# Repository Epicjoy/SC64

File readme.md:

# SummerCart64 - a fully open source N64 flashcart

This project's hardware and casing are modified based on the [SummerCart64](https://github.com/Polprzewodnikowy/SummerCart64) project.

### Description

Experience classic gaming in a new way! SummerCart64 is a fully open-source flash cartridge designed for the Nintendo 64 (N64), perfect for both gamers and developers. Whether you want to relive your childhood memories or develop your own homebrew games, SummerCart64 has you covered.

### Features

-   **Extremely high game compatibility:** Supports N64 games up to 64MB (512Mb), covering the entire N64 game library
-  **Fast I/O**: Supports fast data transfer to ensure smooth gaming experiences，Thanks to a peak transfer rate of approximately 23.8 MiB/s, loading a maximum size game of **64MB** (512Mb) takes roughly 2.7 seconds under optimal conditions
- **RTC Functionality**: Built-in Real-Time Clock (**RTC**) to support games that require time functions.
-  **High-Capacity SD Card Support**: Supports microSD cards up to 2TB, allowing you to store more games and files.
-  **64DD Hardware Emulation**: It can play disk dumps directly! Combo games (N64 cartridge + 64DD disk) and multi-disk 64DD games are also supported.
- **Automatic Save Backup**: Automatically backs up saves during gameplay to protect your progress.
-  **Multi-Region Support**: Compatible with all region N64 consoles, eliminating region lock concerns.
-  **Enough space for your ROMs**: Equipped with **64 MiB SDRAM** and **16 MiB flash** memory to ensure smooth game operation.
-  **Easy Game Management**: Browse, run, and manage your game library directly on your N64 console with the intuitive N64FlashcartMenu.
-  **Full control of boot process:** perfect for trying out custom **IPL3** replacements giving you control right after N64 boots up

### Example

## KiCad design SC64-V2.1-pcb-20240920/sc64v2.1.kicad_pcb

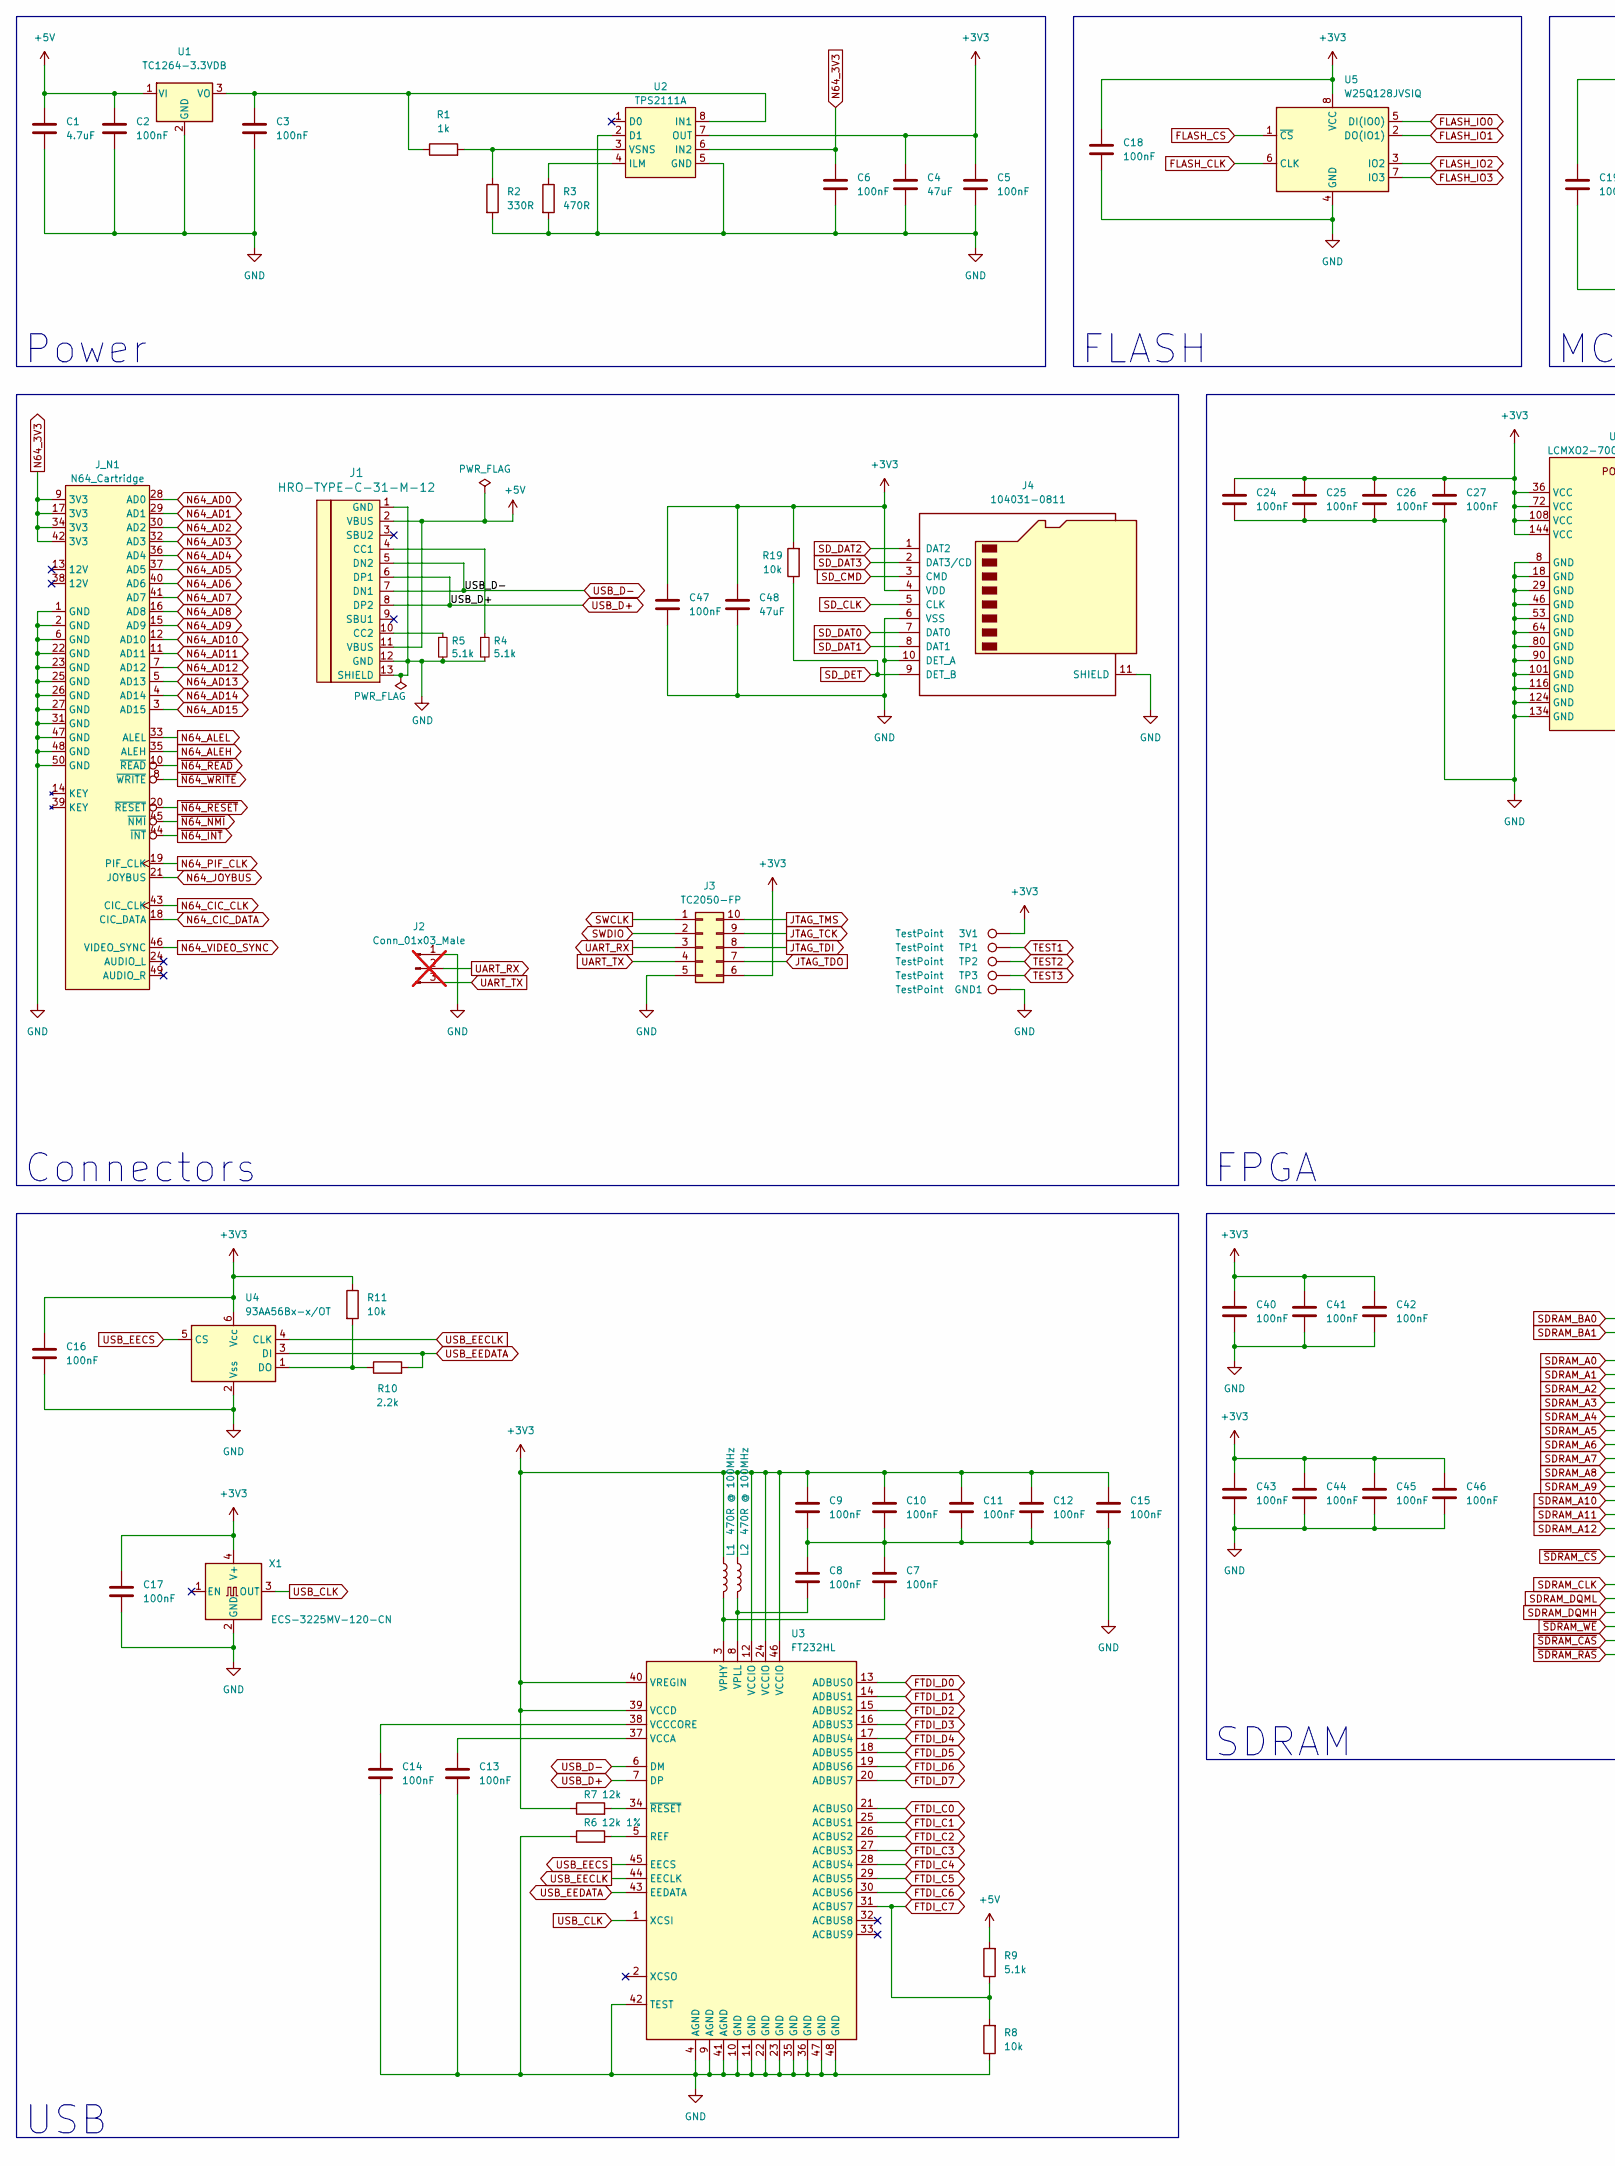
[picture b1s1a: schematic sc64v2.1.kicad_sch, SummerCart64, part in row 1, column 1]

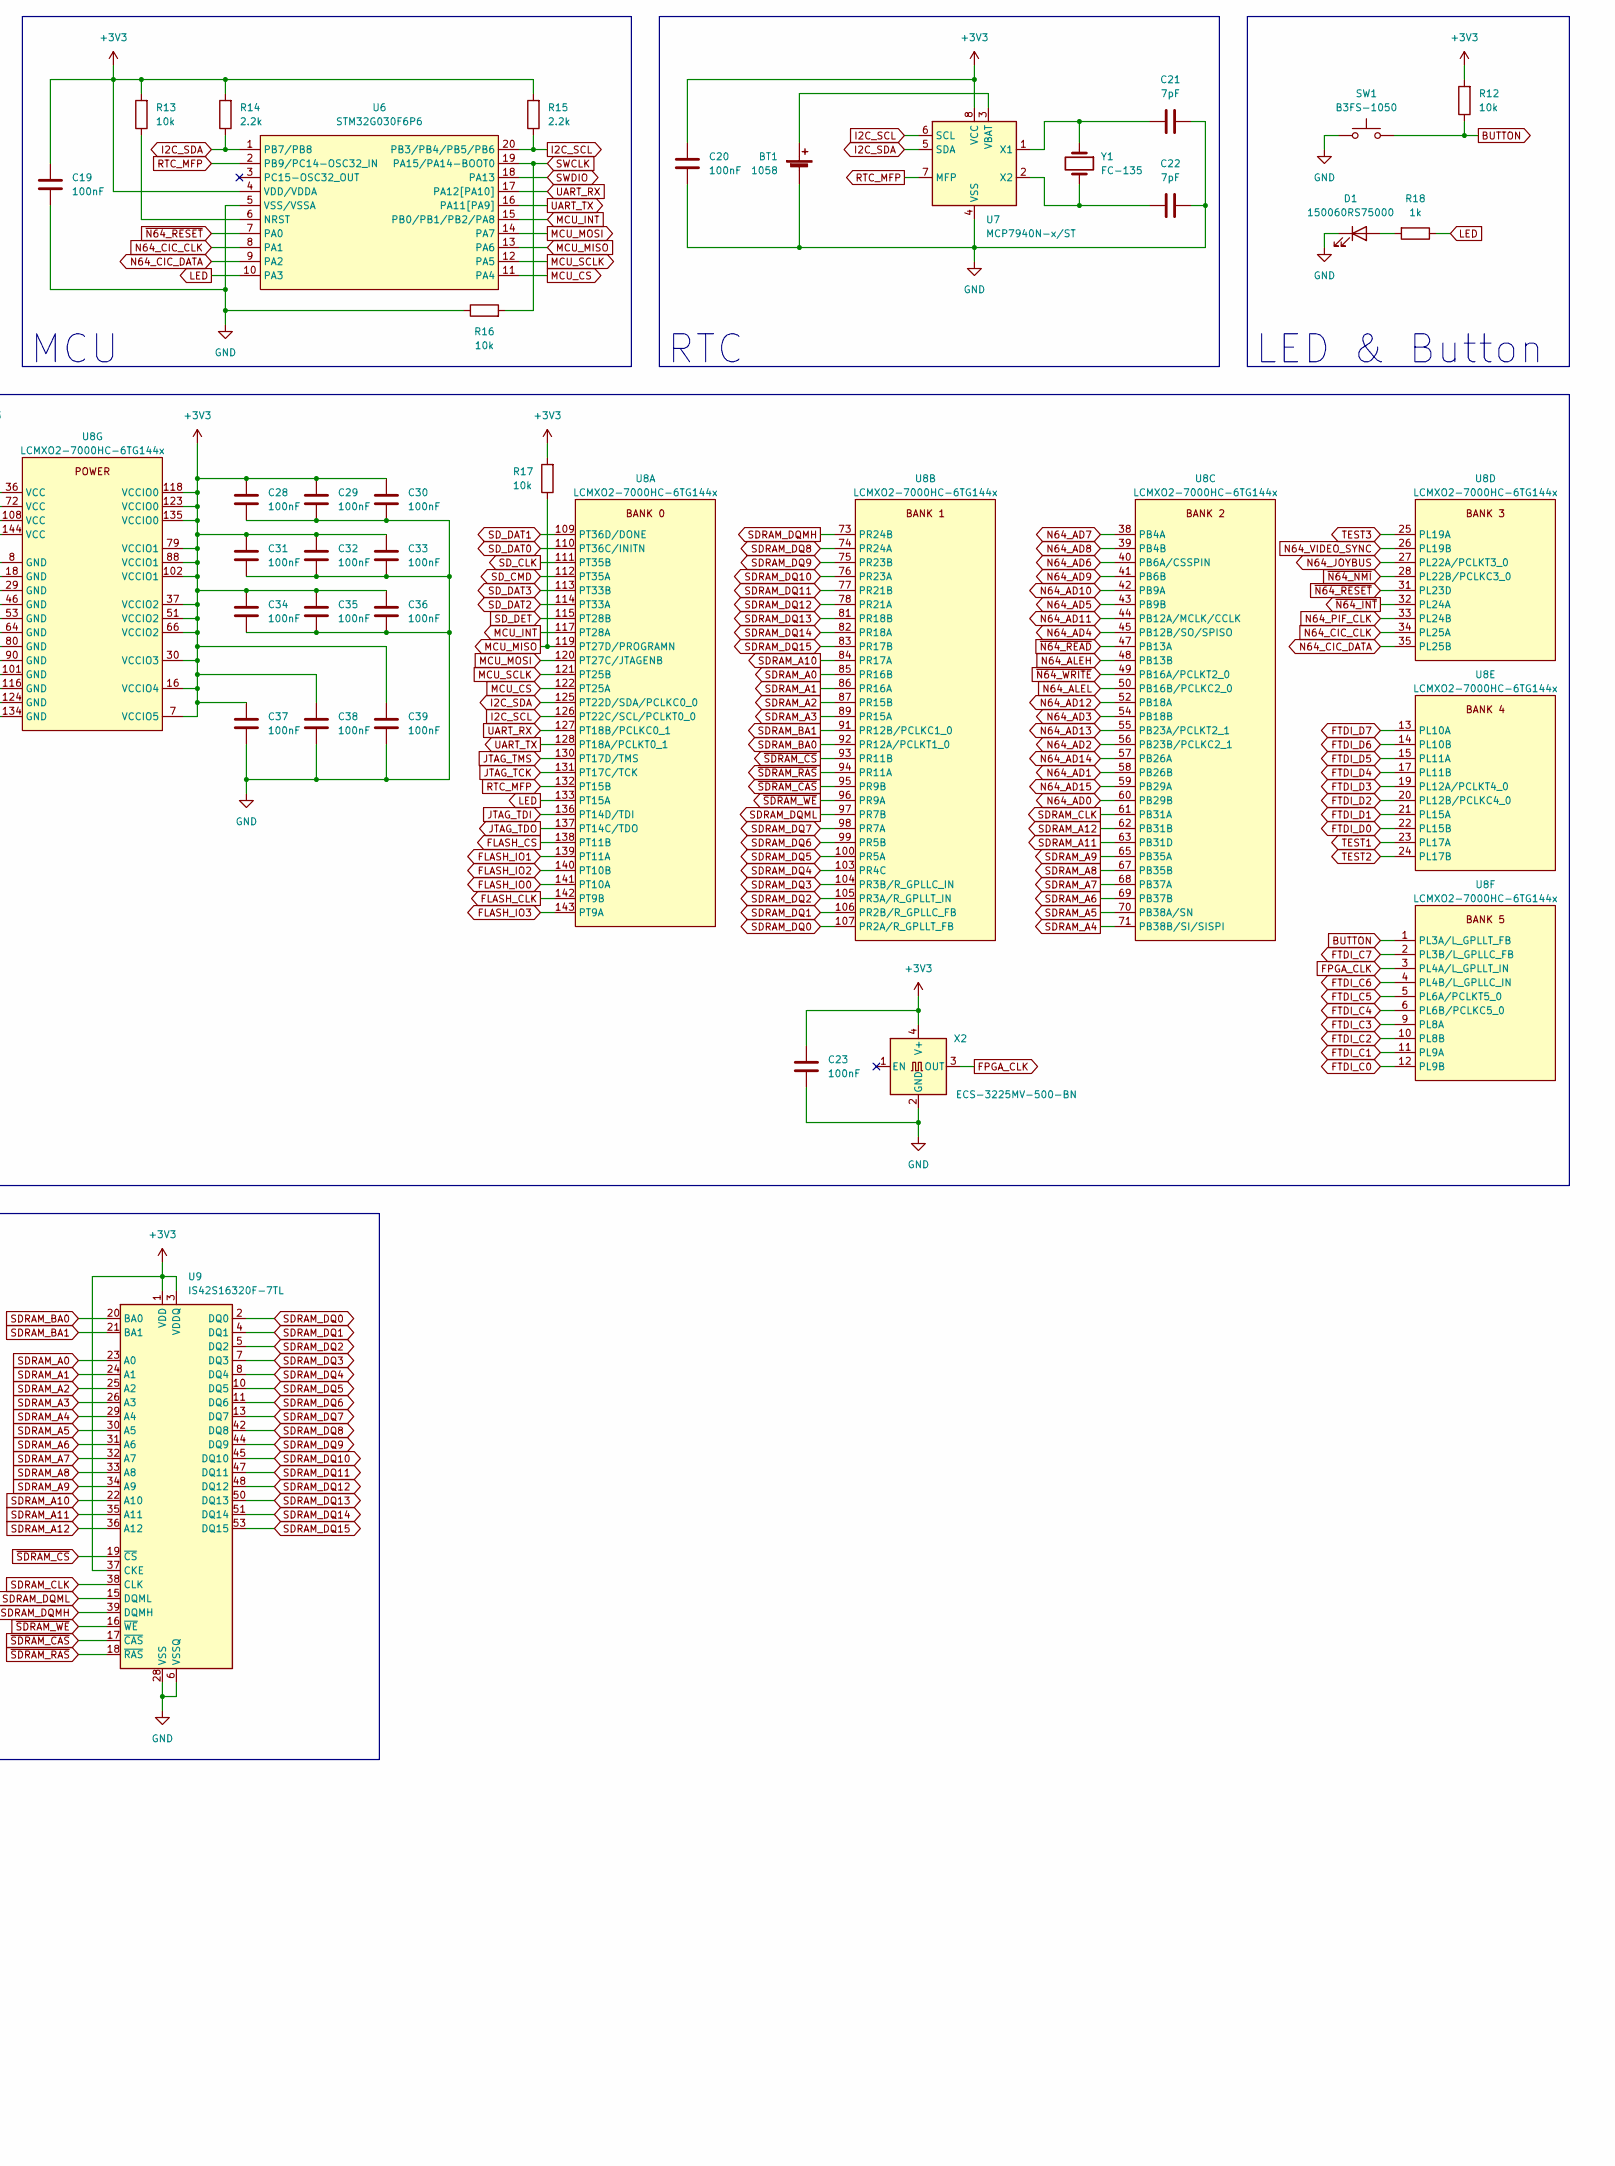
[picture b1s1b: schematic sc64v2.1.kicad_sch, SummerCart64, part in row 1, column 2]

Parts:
3V1: TestPoint; TestPoint_Pad_D1.5mm
BT1: 1058; BatteryHolder_Keystone_1058_1x2032
C1: 4.7uF; C_0603_1608Metric
C2, C3, C5, C6, C7, C8, C9, C10, C11, C12, C13, C14, C15, C16, C17, C18, C19, C20, C23, C24, C25, C26, C27, C28, C29, C30, C31, C32, C33, C34, C35, C36, C37, C38, C39, C40, C41, C42, C43, C44, C45, C46, C47: 100nF; C_0603_1608Metric
C4, C48: 47uF; C_0805_2012Metric
C21, C22: 7pF; C_0603_1608Metric
D1: 150060RS75000; LED_0603_1608Metric
GND1: TestPoint; TestPoint_Pad_D1.5mm
J1: HRO-TYPE-C-31-M-12; HRO-TYPE-C-31-M-12-Assembly; LCSC C165948
J2: Conn_01x03_Male; PinHeader_1x03_P2.54mm_Vertical; not fitted
J3: TC2050-FP; Tag-Connect_TC2050-IDC-FP_2x05_P1.27mm_Vertical
J4: 104031-0811; microSD_HC_Molex_104031-0811
J_N1: N64_Cartridge; N64_Edge
L1, L2: 470R @ 100MHz; L_0603_1608Metric
R1, R18: 1k; R_0603_1608Metric
R2: 330R; R_0603_1608Metric
R3: 470R; R_0603_1608Metric
R4, R5: 5.1k; R_0603_1608Metric; LCSC C25905
R6: 12k 1%; R_0603_1608Metric
R7: 12k; R_0603_1608Metric
R8, R11, R12, R13, R16, R17, R19: 10k; R_0603_1608Metric
R9: 5.1k; R_0603_1608Metric
R10, R14, R15: 2.2k; R_0603_1608Metric
SW1: B3FS-1050; SW_SPST_Omron_B3FS-105xP
TP1, TP2, TP3: TestPoint; TestPoint_Pad_D1.5mm
U1: TC1264-3.3VDB; SOT-223-3_TabPin2
U2: TPS2111A; TSSOP-8_4.4x3mm_P0.65mm
U3: FT232HL; LQFP-48_7x7mm_P0.5mm
U4: 93AA56Bx-x/OT; SOT-23-6
U5: W25Q128JVSIQ; SOIC-8_5.23x5.23mm_P1.27mm
U6: STM32G030F6P6; TSSOP-20_4.4x6.5mm_P0.65mm
U7: MCP7940N-x/ST; TSSOP-8_4.4x3mm_P0.65mm
U8: LCMXO2-7000HC-6TG144x; TQFP-144_20x20mm_P0.5mm
U9: IS42S16320F-7TL; TSOP-II-54_22.2x10.16mm_P0.8mm
X1: ECS-3225MV-120-CN; Oscillator_SMD_SeikoEpson_SG8002CE-4Pin_3.2x2.5mm
X2: ECS-3225MV-500-BN; Oscillator_SMD_SeikoEpson_SG8002CE-4Pin_3.2x2.5mm
Y1: FC-135; Crystal_SMD_3215-2Pin_3.2x1.5mm

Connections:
+3V3: 3V1.1, C4.1, C5.1, C9.1, C10.1, C11.1, C12.1, C15.1, C16.2, C17.1, C18.1, C19.1, C20.1, C23.1, C24.1, C25.1, C26.1, C27.1, C28.1, C29.1, C30.1, C31.1, C32.1, C33.1, C34.1, C35.1, C36.1, C37.1, C38.1, C39.1, C40.1, C41.1, C42.1, C43.1, C44.1, C45.1, C46.1, C47.1, C48.1, J3.6, J4.4 (VDD), L1.1, L2.1, R7.1, R11.1, R12.2, R13.2, R14.2, R15.2, R17.2, R19.2, U2.7 (OUT), U3.12 (VCCIO), U3.24 (VCCIO), U3.39 (VCCD), U3.40 (VREGIN), U3.46 (VCCIO), U4.6 (Vсс), U5.8 (VCC), U6.4 (VDD/VDDA), U7.8 (VCC), U8.7 (VCCIO5), U8.16 (VCCIO4), U8.30 (VCCIO3), U8.36 (VCC), U8.37 (VCCIO2), U8.51 (VCCIO2), U8.66 (VCCIO2), U8.72 (VCC), U8.79 (VCCIO1), U8.88 (VCCIO1), U8.102 (VCCIO1), U8.108 (VCC), U8.118 (VCCIO0), U8.123 (VCCIO0), U8.135 (VCCIO0), U8.144 (VCC), U9.1 (VDD), U9.3 (VDDQ), U9.9 (VDDQ), U9.14 (VDD), U9.27 (VDD), U9.37 (CKE), U9.43 (VDDQ), U9.49 (VDDQ), X1.4 (V+), X2.4 (V+)
+5V: C1.1, C2.1, J1.2 (VBUS), J1.11 (VBUS), R9.2, U1.1 (VI)
BUTTON: R12.1, SW1.2, U8.1 (PL3A/L_GPLLT_FB)
FLASH_CLK: U5.6 (CLK), U8.142 (PT9B)
FLASH_CS: U5.1 (~CS), U8.138 (PT11B)
FLASH_IO0: U5.5 (DI(IO0)), U8.141 (PT10A)
FLASH_IO1: U5.2 (DO(IO1)), U8.139 (PT11A)
FLASH_IO2: U5.3 (IO2), U8.140 (PT10B)
FLASH_IO3: U5.7 (IO3), U8.143 (PT9A)
FPGA_CLK: U8.3 (PL4A/L_GPLLT_IN), X2.3 (OUT)
FTDI_C0: U3.21 (ACBUS0), U8.12 (PL9B)
FTDI_C1: U3.25 (ACBUS1), U8.11 (PL9A)
FTDI_C2: U3.26 (ACBUS2), U8.10 (PL8B)
FTDI_C3: U3.27 (ACBUS3), U8.9 (PL8A)
FTDI_C4: U3.28 (ACBUS4), U8.6 (PL6B/PCLKC5_0)
FTDI_C5: U3.29 (ACBUS5), U8.5 (PL6A/PCLKT5_0)
FTDI_C6: U3.30 (ACBUS6), U8.4 (PL4B/L_GPLLC_IN)
FTDI_C7: R8.2, R9.1, U3.31 (ACBUS7), U8.2 (PL3B/L_GPLLC_FB)
FTDI_D0: U3.13 (ADBUS0), U8.22 (PL15B)
FTDI_D1: U3.14 (ADBUS1), U8.21 (PL15A)
FTDI_D2: U3.15 (ADBUS2), U8.20 (PL12B/PCLKC4_0)
FTDI_D3: U3.16 (ADBUS3), U8.19 (PL12A/PCLKT4_0)
FTDI_D4: U3.17 (ADBUS4), U8.17 (PL11B)
FTDI_D5: U3.18 (ADBUS5), U8.15 (PL11A)
FTDI_D6: U3.19 (ADBUS6), U8.14 (PL10B)
FTDI_D7: U3.20 (ADBUS7), U8.13 (PL10A)
GND: BT1.2 (-), C1.2, C2.2, C3.2, C4.2, C5.2, C6.2, C7.1, C8.2, C9.2, C10.2, C11.2, C12.2, C13.1, C14.1, C15.2, C16.1, C17.2, C18.2, C19.2, C20.2, C21.2, C22.1, C23.2, C24.2, C25.2, C26.2, C27.2, C28.2, C29.2, C30.2, C31.2, C32.2, C33.2, C34.2, C35.2, C36.2, C37.2, C38.2, C39.2, C40.2, C41.2, C42.2, C43.2, C44.2, C45.2, C46.2, C47.2, C48.2, D1.1 (K), GND1.1, J1.1 (GND), J1.12 (GND), J1.13 (SHIELD), J2.1, J3.5, J4.6 (VSS), J4.10 (DET_A), J4.11 (SHIELD), J4.12, J4.13, J_N1.1 (GND), J_N1.2 (GND), J_N1.6 (GND), J_N1.22 (GND), J_N1.23 (GND), J_N1.25 (GND), J_N1.26 (GND), J_N1.27 (GND), J_N1.31 (GND), J_N1.47 (GND), J_N1.48 (GND), J_N1.50 (GND), R2.2, R3.2, R4.2, R5.2, R6.1, R8.1, R16.1, SW1.1, U1.2 (GND), U2.2 (D1), U2.5 (GND), U3.4 (AGND), U3.9 (AGND), U3.10 (GND), U3.11 (GND), U3.22 (GND), U3.23 (GND), U3.35 (GND), U3.36 (GND), U3.41 (AGND), U3.42 (TEST), U3.47 (GND), U3.48 (GND), U4.2 (Vss), U5.4 (GND), U6.5 (VSS/VSSA), U7.4 (VSS), U8.8 (GND), U8.18 (GND), U8.29 (GND), U8.46 (GND), U8.53 (GND), U8.64 (GND), U8.80 (GND), U8.90 (GND), U8.101 (GND), U8.116 (GND), U8.124 (GND), U8.134 (GND), U9.6 (VSSQ), U9.12 (VSSQ), U9.28 (VSS), U9.41 (VSS), U9.46 (VSSQ), U9.52 (VSSQ), U9.54 (VSS), X1.2 (GND), X2.2 (GND)
I2C_SCL: R15.1, U6.20 (PB3/PB4/PB5/PB6), U7.6 (SCL), U8.126 (PT22C/SCL/PCLKT0_0)
I2C_SDA: R14.1, U6.1 (PB7/PB8), U7.5 (SDA), U8.125 (PT22D/SDA/PCLKC0_0)
JTAG_TCK: J3.9, U8.131 (PT17C/TCK)
JTAG_TDI: J3.8, U8.136 (PT14D/TDI)
JTAG_TDO: J3.7, U8.137 (PT14C/TDO)
JTAG_TMS: J3.10, U8.130 (PT17D/TMS)
LED: R18.1, U6.10 (PA3), U8.133 (PT15A)
MCU_CS: U6.11 (PA4), U8.122 (PT25A)
MCU_INT: U6.15 (PB0/PB1/PB2/PA8), U8.117 (PT28A)
MCU_MISO: R17.1, U6.13 (PA6), U8.119 (PT27D/PROGRAMN)
MCU_MOSI: U6.14 (PA7), U8.120 (PT27C/JTAGENB)
MCU_SCLK: U6.12 (PA5), U8.121 (PT25B)
N64_3V3: C6.1, J_N1.9 (3V3), J_N1.17 (3V3), J_N1.34 (3V3), J_N1.42 (3V3), U2.6 (IN2)
N64_AD0: J_N1.28 (AD0), U8.60 (PB29B)
N64_AD1: J_N1.29 (AD1), U8.58 (PB26B)
N64_AD2: J_N1.30 (AD2), U8.56 (PB23B/PCLKC2_1)
N64_AD3: J_N1.32 (AD3), U8.54 (PB18B)
N64_AD4: J_N1.36 (AD4), U8.45 (PB12B/SO/SPISO)
N64_AD5: J_N1.37 (AD5), U8.43 (PB9B)
N64_AD6: J_N1.40 (AD6), U8.40 (PB6A/CSSPIN)
N64_AD7: J_N1.41 (AD7), U8.38 (PB4A)
N64_AD8: J_N1.16 (AD8), U8.39 (PB4B)
N64_AD9: J_N1.15 (AD9), U8.41 (PB6B)
N64_AD10: J_N1.12 (AD10), U8.42 (PB9A)
N64_AD11: J_N1.11 (AD11), U8.44 (PB12A/MCLK/CCLK)
N64_AD12: J_N1.7 (AD12), U8.52 (PB18A)
N64_AD13: J_N1.5 (AD13), U8.55 (PB23A/PCLKT2_1)
N64_AD14: J_N1.4 (AD14), U8.57 (PB26A)
N64_AD15: J_N1.3 (AD15), U8.59 (PB29A)
N64_ALEH: J_N1.35 (ALEH), U8.48 (PB13B)
N64_ALEL: J_N1.33 (ALEL), U8.50 (PB16B/PCLKC2_0)
N64_CIC_CLK: J_N1.43 (CIC_CLK), U6.8 (PA1), U8.34 (PL25A)
N64_CIC_DATA: J_N1.18 (CIC_DATA), U6.9 (PA2), U8.35 (PL25B)
N64_JOYBUS: J_N1.21 (JOYBUS), U8.27 (PL22A/PCLKT3_0)
N64_PIF_CLK: J_N1.19 (PIF_CLK), U8.33 (PL24B)
N64_VIDEO_SYNC: J_N1.46 (VIDEO_SYNC), U8.26 (PL19B)
unnamed: BT1.1 (+), U7.3 (VBAT)
unnamed: D1.2 (A), R18.2
unnamed: C3.1, R1.1, U1.3 (VO), U2.8 (IN1)
unnamed: R3.1, U2.4 (ILM)
unnamed: R1.2, R2.1, U2.3 (VSNS)
unnamed: R6.2, U3.5 (REF)
unnamed: C13.2, U3.37 (VCCA)
unnamed: C14.2, U3.38 (VCCCORE)
unnamed: C7.2, L1.2, U3.3 (VPHY)
unnamed: C8.1, L2.2, U3.8 (VPLL)
unnamed: R7.2, U3.34 (~RESET)
unnamed: R10.1, R11.2, U4.1 (DO)
unnamed: R13.1, U6.6 (NRST)
unnamed: C21.1, U7.1 (X1), Y1.1
unnamed: C22.2, U7.2 (X2), Y1.2
unnamed: J1.4 (CC1), R4.1
unnamed: J1.10 (CC2), R5.1
RTC_MFP: U6.2 (PB9/PC14-OSC32_IN), U7.7 (MFP), U8.132 (PT15B)
SDRAM_A0: U8.85 (PR16B), U9.23 (A0)
SDRAM_A1: U8.86 (PR16A), U9.24 (A1)
SDRAM_A2: U8.87 (PR15B), U9.25 (A2)
SDRAM_A3: U8.89 (PR15A), U9.26 (A3)
SDRAM_A4: U8.71 (PB38B/SI/SISPI), U9.29 (A4)
SDRAM_A5: U8.70 (PB38A/SN), U9.30 (A5)
SDRAM_A6: U8.69 (PB37B), U9.31 (A6)
SDRAM_A7: U8.68 (PB37A), U9.32 (A7)
SDRAM_A8: U8.67 (PB35B), U9.33 (A8)
SDRAM_A9: U8.65 (PB35A), U9.34 (A9)
SDRAM_A10: U8.84 (PR17A), U9.22 (A10)
SDRAM_A11: U8.63 (PB31D), U9.35 (A11)
SDRAM_A12: U8.62 (PB31B), U9.36 (A12)
SDRAM_BA0: U8.92 (PR12A/PCLKT1_0), U9.20 (BA0)
SDRAM_BA1: U8.91 (PR12B/PCLKC1_0), U9.21 (BA1)
SDRAM_CLK: U8.61 (PB31A), U9.38 (CLK)
SDRAM_DQ0: U8.107 (PR2A/R_GPLLT_FB), U9.2 (DQ0)
SDRAM_DQ1: U8.106 (PR2B/R_GPLLC_FB), U9.4 (DQ1)
SDRAM_DQ2: U8.105 (PR3A/R_GPLLT_IN), U9.5 (DQ2)
SDRAM_DQ3: U8.104 (PR3B/R_GPLLC_IN), U9.7 (DQ3)
SDRAM_DQ4: U8.103 (PR4C), U9.8 (DQ4)
SDRAM_DQ5: U8.100 (PR5A), U9.10 (DQ5)
SDRAM_DQ6: U8.99 (PR5B), U9.11 (DQ6)
SDRAM_DQ7: U8.98 (PR7A), U9.13 (DQ7)
SDRAM_DQ8: U8.74 (PR24A), U9.42 (DQ8)
SDRAM_DQ9: U8.75 (PR23B), U9.44 (DQ9)
SDRAM_DQ10: U8.76 (PR23A), U9.45 (DQ10)
SDRAM_DQ11: U8.77 (PR21B), U9.47 (DQ11)
SDRAM_DQ12: U8.78 (PR21A), U9.48 (DQ12)
SDRAM_DQ13: U8.81 (PR18B), U9.50 (DQ13)
SDRAM_DQ14: U8.82 (PR18A), U9.51 (DQ14)
SDRAM_DQ15: U8.83 (PR17B), U9.53 (DQ15)
SDRAM_DQMH: U8.73 (PR24B), U9.39 (DQMH)
SDRAM_DQML: U8.97 (PR7B), U9.15 (DQML)
SD_CLK: J4.5 (CLK), U8.111 (PT35B)
SD_CMD: J4.3 (CMD), U8.112 (PT35A)
SD_DAT0: J4.7 (DAT0), U8.110 (PT36C/INITN)
SD_DAT1: J4.8 (DAT1), U8.109 (PT36D/DONE)
SD_DAT2: J4.1 (DAT2), U8.114 (PT33A)
SD_DAT3: J4.2 (DAT3/CD), U8.113 (PT33B)
SD_DET: J4.9 (DET_B), R19.1, U8.115 (PT28B)
SWCLK: J3.1, R16.2, U6.19 (PA15/PA14-BOOT0)
SWDIO: J3.2, U6.18 (PA13)
TEST1: TP1.1, U8.23 (PL17A)
TEST2: TP2.1, U8.24 (PL17B)
TEST3: TP3.1, U8.25 (PL19A)
UART_RX: J2.2, J3.3, U6.17 (PA12[PA10]), U8.127 (PT18B/PCLKC0_1)
UART_TX: J2.3, J3.4, U6.16 (PA11[PA9]), U8.128 (PT18A/PCLKT0_1)
USB_CLK: U3.1 (XCSI), X1.3 (OUT)
USB_D+: J1.6 (DP1), J1.8 (DP2), U3.7 (DP)
USB_D-: J1.5 (DN2), J1.7 (DN1), U3.6 (DM)
USB_EECLK: U3.44 (EECLK), U4.4 (CLK)
USB_EECS: U3.45 (EECS), U4.5 (CS)
USB_EEDATA: R10.2, U3.43 (EEDATA), U4.3 (DI)
~N64_INT: J_N1.44 (~INT), U8.32 (PL24A)
~N64_NMI: J_N1.45 (~NMI), U8.28 (PL22B/PCLKC3_0)
~N64_READ: J_N1.10 (~READ), U8.47 (PB13A)
~N64_RESET: J_N1.20 (~RESET), U6.7 (PA0), U8.31 (PL23D)
~N64_WRITE: J_N1.8 (~WRITE), U8.49 (PB16A/PCLKT2_0)
~SDRAM_CAS: U8.95 (PR9B), U9.17 (~CAS)
~SDRAM_CS: U8.93 (PR11B), U9.19 (~CS)
~SDRAM_RAS: U8.94 (PR11A), U9.18 (~RAS)
~SDRAM_WE: U8.96 (PR9A), U9.16 (~WE)

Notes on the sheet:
Power
USB
LED & Button
RTC
Connectors
MCU
FPGA
FLASH
SDRAM

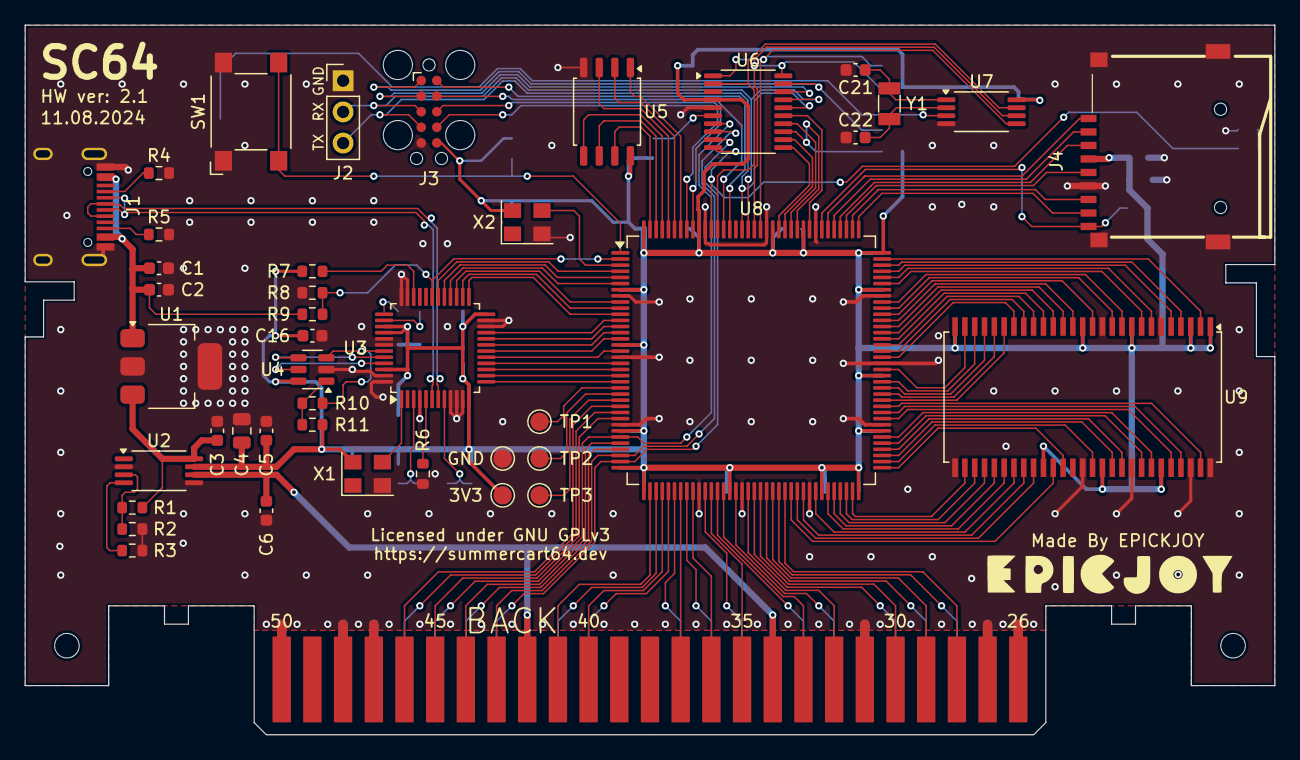
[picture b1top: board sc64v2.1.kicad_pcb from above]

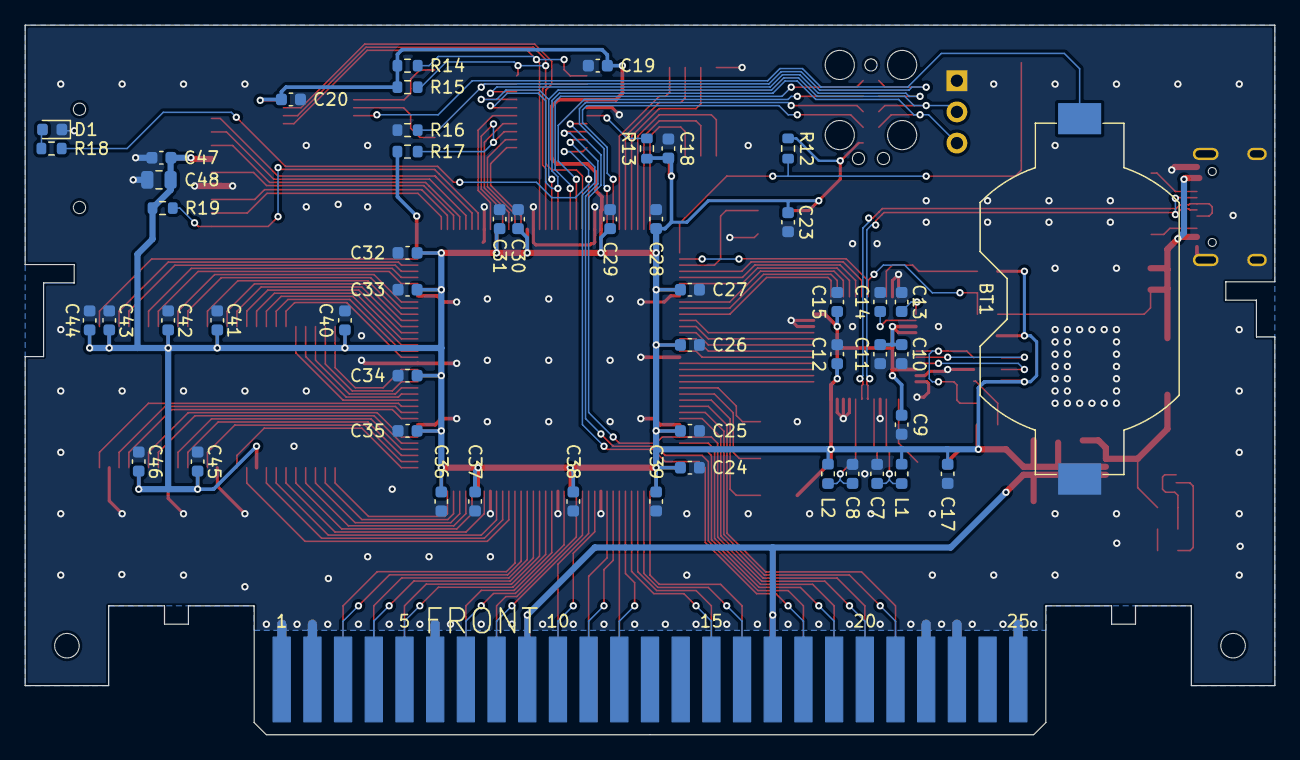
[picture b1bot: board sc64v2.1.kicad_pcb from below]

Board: 2 copper layers, 101.8 x 57.8 mm, 94 parts (51 on the bottom side), 144 nets.

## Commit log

2025-01-07 Create usermanual
2025-01-07 Create 1

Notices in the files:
SC64-V2.1-pcb-20240920/sc64v2.1.kicad_pcb:
Licensed under GNU GPLv3
© 2020 - 2024
